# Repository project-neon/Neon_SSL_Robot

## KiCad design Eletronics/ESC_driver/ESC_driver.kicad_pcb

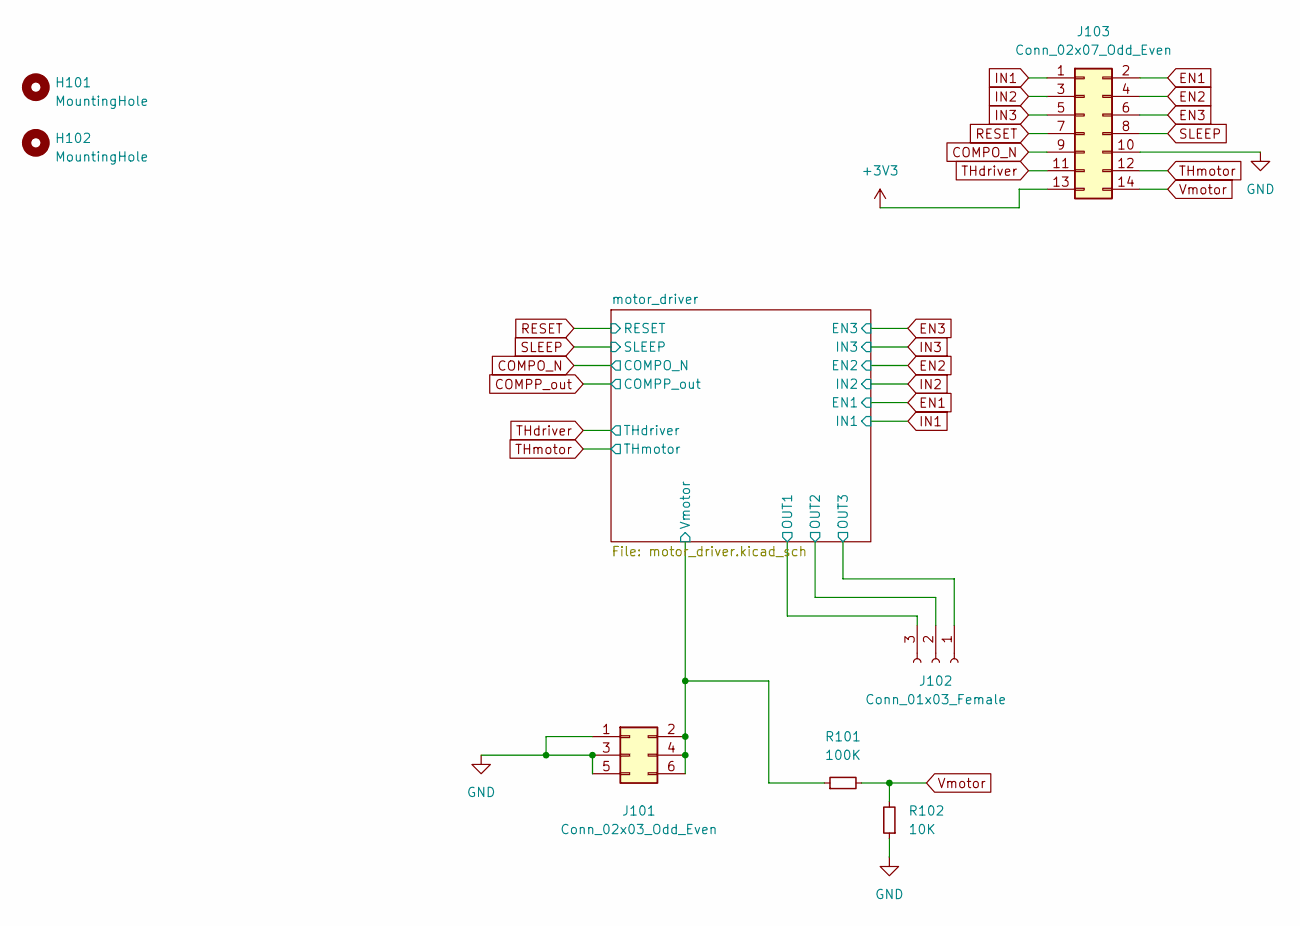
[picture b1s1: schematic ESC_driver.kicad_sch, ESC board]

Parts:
H101, H102: MountingHole; MountingHole_2.5mm
J101: Conn_02x03_Odd_Even; PinHeader_2x03_P2.54mm_Vertical; LCSC C65114
J102: Conn_01x03_Female; PinHeader_1x03_P2.54mm_Vertical; LCSC C6332196
J103: Conn_02x07_Odd_Even; PinHeader_2x07_P2.54mm_Vertical; LCSC C71397
R101: 100K; R_0603_1608Metric_Pad0.98x0.95mm_HandSolder; LCSC C14675
R102: 10K; R_0603_1608Metric_Pad0.98x0.95mm_HandSolder; LCSC C2930027

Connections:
+3V3: J103.13; also elsewhere on the board
/motor_driver/OUT1: J102.3; also elsewhere on the board
/motor_driver/OUT2: J102.2; also elsewhere on the board
/motor_driver/OUT3: J102.1; also elsewhere on the board
/motor_driver/VM_0.1_100uf: J101.2, J101.4, J101.6, R101.1; also elsewhere on the board
COMPO_N: J103.9; also elsewhere on the board
EN1: J103.2; also elsewhere on the board
EN2: J103.4; also elsewhere on the board
EN3: J103.6; also elsewhere on the board
GND: J101.1, J101.3, J101.5, J103.10, R102.1; also elsewhere on the board
IN1: J103.1; also elsewhere on the board
IN2: J103.3; also elsewhere on the board
IN3: J103.5; also elsewhere on the board
RESET: J103.7; also elsewhere on the board
SLEEP: J103.8; also elsewhere on the board
THdriver: J103.11; also elsewhere on the board
THmotor: J103.12; also elsewhere on the board
Vmotor: J103.14, R101.2, R102.2

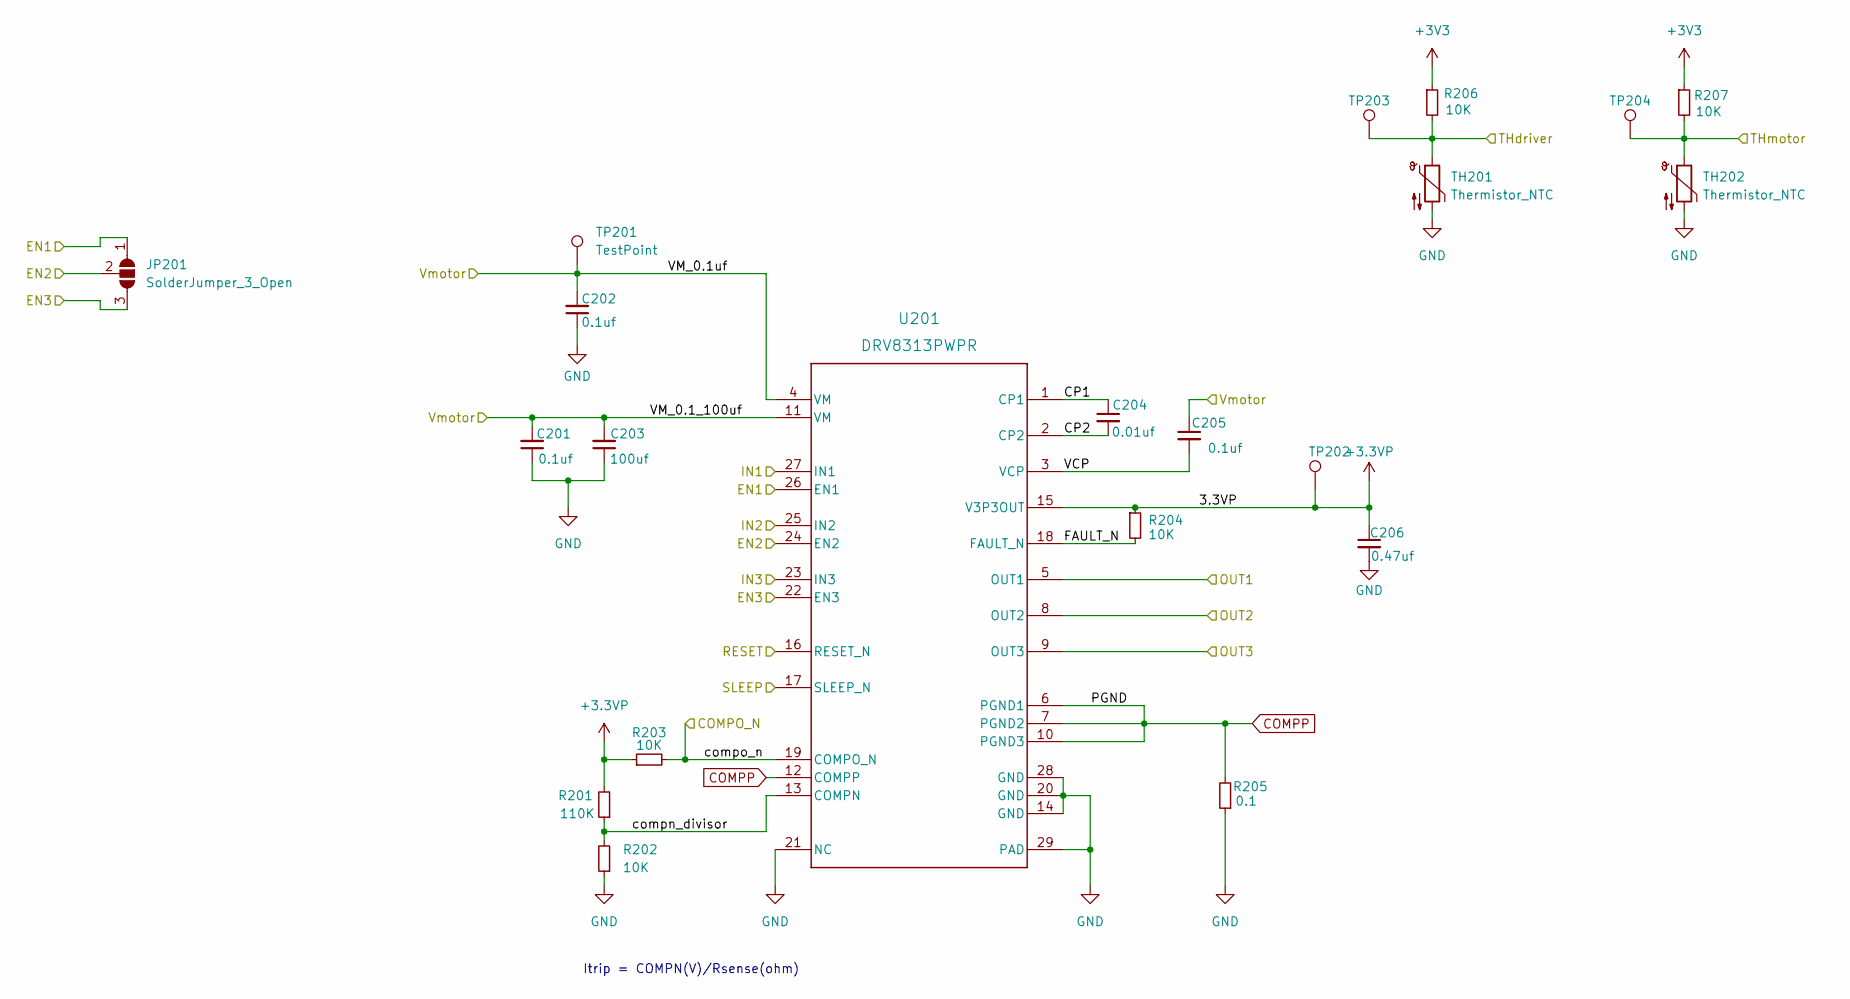
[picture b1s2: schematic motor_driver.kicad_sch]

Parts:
C201, C202, C205: 0.1uf; R_0603_1608Metric_Pad0.98x0.95mm_HandSolder; LCSC C14663
C203: 100uf; C_Elec_6.3x7.7; LCSC C72477
C204: 0.01uf; R_0603_1608Metric_Pad0.98x0.95mm_HandSolder; LCSC C1589
C206: 0.47uf; R_0603_1608Metric_Pad0.98x0.95mm_HandSolder; LCSC C105526
JP201: SolderJumper_3_Open; SolderJumper-3_P1.3mm_Open_RoundedPad1.0x1.5mm
R201: 110K; R_0603_1608Metric_Pad0.98x0.95mm_HandSolder; LCSC C25805
R202, R203, R204, R206, R207: 10K; R_0603_1608Metric_Pad0.98x0.95mm_HandSolder; LCSC C2930027
R205: 0.1; R_2512_6332Metric; LCSC C25466
TH201: Thermistor_NTC; R_0603_1608Metric_Pad0.98x0.95mm_HandSolder; LCSC C406719
TH202: Thermistor_NTC; PinHeader_1x02_P2.54mm_Vertical; LCSC C492401
TP201, TP202, TP203, TP204: TestPoint; TestPoint_Pad_D1.0mm
U201: DRV8313PWPR; PWP0028F_N; LCSC C92482

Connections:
+3.3VP: C206.1, R201.2, R203.1, R204.1, TP202.1, U201.15 (V3P3OUT)
+3V3: R206.1, R207.1; also elsewhere on the board
/motor_driver/CP1: C204.1, U201.1 (CP1)
/motor_driver/CP2: C204.2, U201.2 (CP2)
/motor_driver/FAULT_N: R204.2, U201.18 (FAULT_N)
/motor_driver/OUT1: U201.5 (OUT1); also elsewhere on the board
/motor_driver/OUT2: U201.8 (OUT2); also elsewhere on the board
/motor_driver/OUT3: U201.9 (OUT3); also elsewhere on the board
/motor_driver/VCP: C205.2, U201.3 (VCP)
/motor_driver/VM_0.1_100uf: C201.2, C202.2, C203.2, C205.1, TP201.1, U201.4 (VM), U201.11 (VM); also elsewhere on the board
/motor_driver/compn_divisor: R201.1, R202.2, U201.13 (COMPN)
COMPO_N: R203.2, U201.19 (COMPO_N); also elsewhere on the board
COMPP: R205.2, U201.6 (PGND1), U201.7 (PGND2), U201.10 (PGND3), U201.12 (COMPP)
EN1: JP201.1 (A), U201.26 (EN1); also elsewhere on the board
EN2: JP201.2 (C), U201.24 (EN2); also elsewhere on the board
EN3: JP201.3 (B), U201.22 (EN3); also elsewhere on the board
GND: C201.1, C202.1, C203.1, C206.2, R202.1, R205.1, TH201.2, TH202.2, U201.14 (GND), U201.20 (GND), U201.21 (NC), U201.28 (GND), U201.29 (PAD); also elsewhere on the board
IN1: U201.27 (IN1); also elsewhere on the board
IN2: U201.25 (IN2); also elsewhere on the board
IN3: U201.23 (IN3); also elsewhere on the board
RESET: U201.16 (RESET_N); also elsewhere on the board
SLEEP: U201.17 (SLEEP_N); also elsewhere on the board
THdriver: R206.2, TH201.1, TP203.1; also elsewhere on the board
THmotor: R207.2, TH202.1, TP204.1; also elsewhere on the board

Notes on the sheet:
Itrip = COMPN(V)/Rsense(ohm)

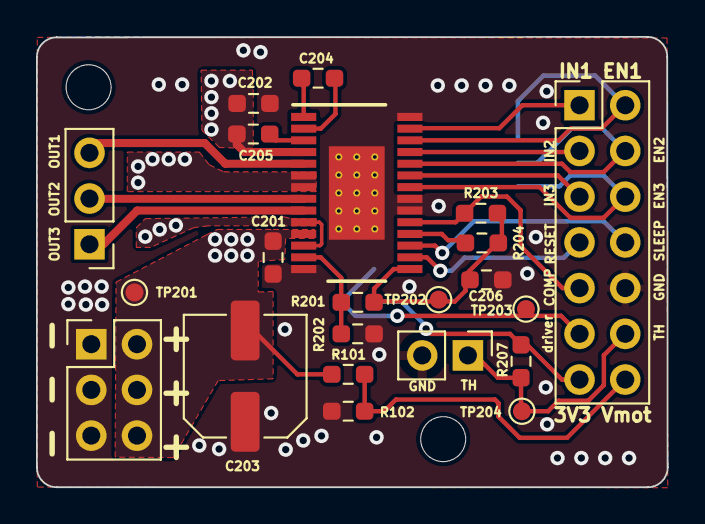
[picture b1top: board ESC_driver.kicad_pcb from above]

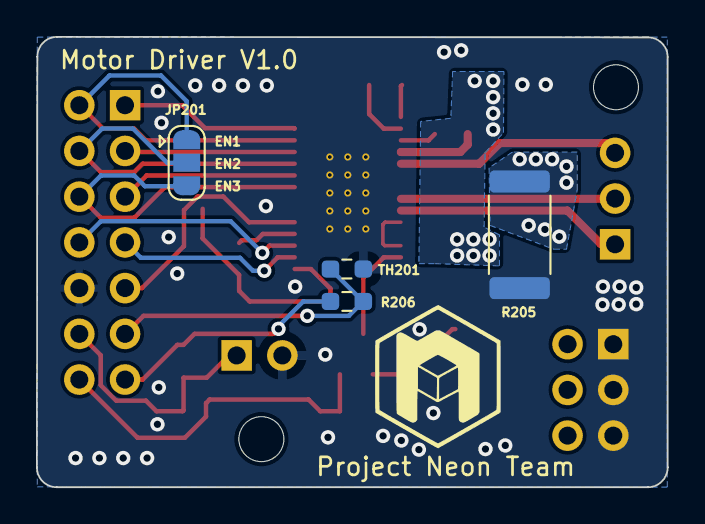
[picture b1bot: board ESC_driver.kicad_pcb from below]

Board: 2 copper layers, 35.0 x 25.0 mm, 28 parts (4 on the bottom side), 25 nets.

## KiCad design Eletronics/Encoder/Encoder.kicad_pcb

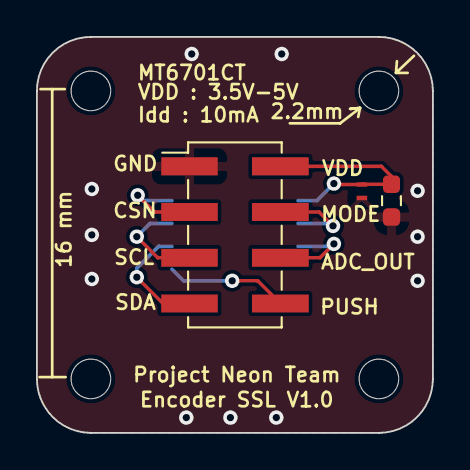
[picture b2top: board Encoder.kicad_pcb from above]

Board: 2 copper layers, 22.0 x 22.0 mm, 8 parts (1 on the bottom side), 8 nets.

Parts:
C201: 0.1UF; R_0603_1608Metric_Pad0.98x0.95mm_HandSolder
D201: VESD05A1B-HD1-GS08; VESD05A1B-HD1
H201, H202, H203, H204: MountingHole; MountingHole_2.2mm_M2
J201: Conn_02x04_Counter_Clockwise; PinHeader_2x04_P2.54mm_Vertical_SMD
U201: MT6701CT; SO-8_5.3x6.2mm_P1.27mm

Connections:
+3V3: C201.1, D201.1 (A1), J201.2, U201.1 (VDD)
ADC_out: J201.6, U201.3 (OUT)
A/SDA/DO: J201.7, U201.6 (A)
B/SCL/CLK: J201.5, U201.7 (B)
GND: C201.2, D201.2 (A2), J201.1, U201.4 (GND)
MODE: J201.4, U201.2 (MODE)
Z/CSN: J201.3, U201.8 (Z)
push: J201.8, U201.5 (PUSH)

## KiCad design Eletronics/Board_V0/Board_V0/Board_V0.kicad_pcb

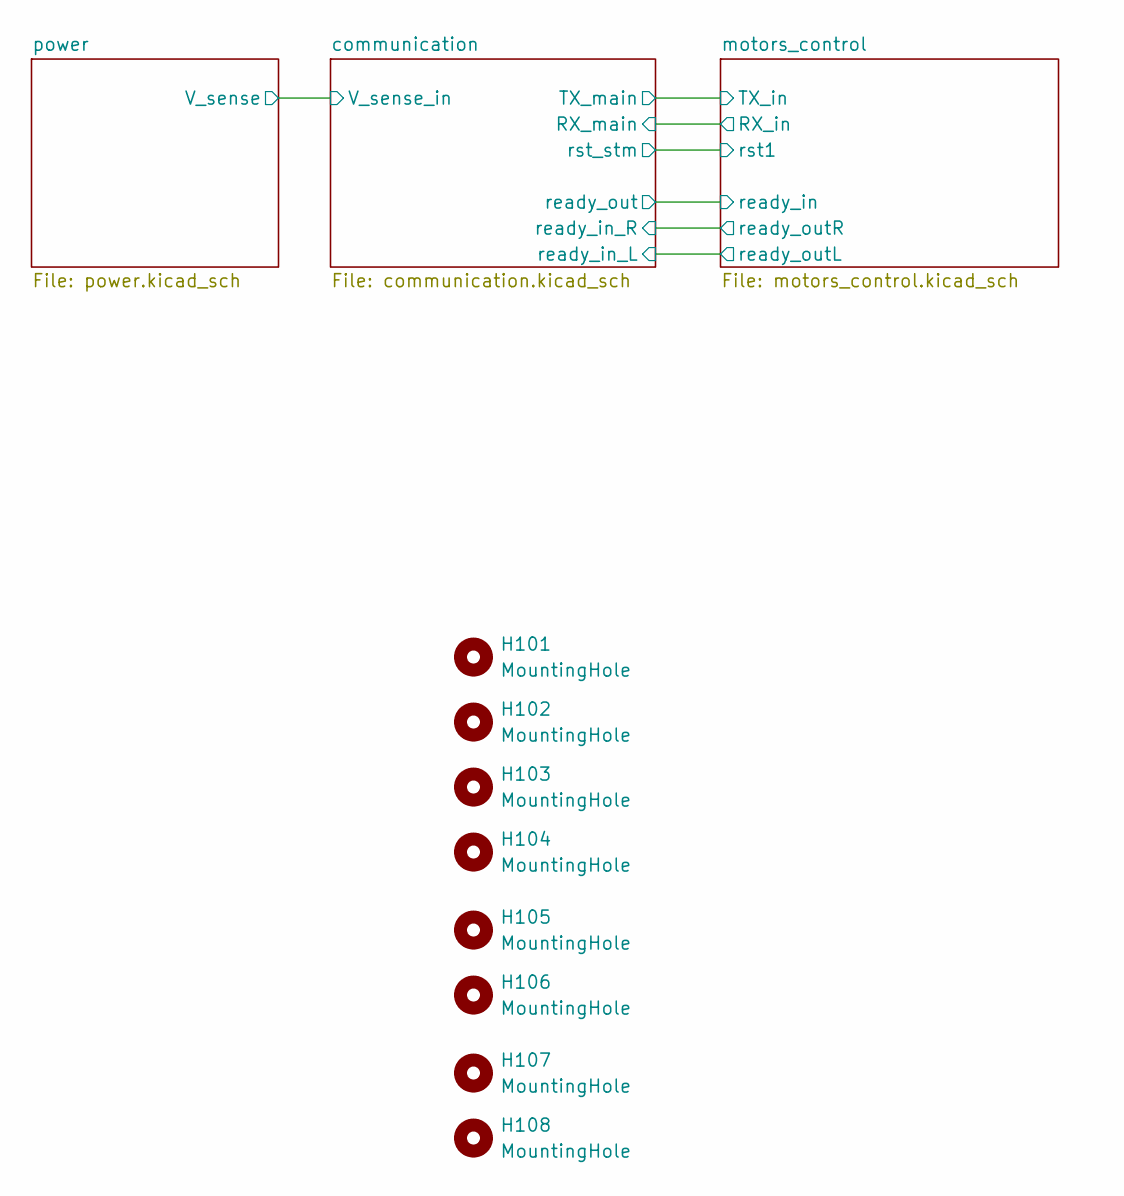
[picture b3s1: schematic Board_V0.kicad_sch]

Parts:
H101, H102, H103, H104, H105, H106, H107, H108: MountingHole; MountingHole_3.2mm_M3

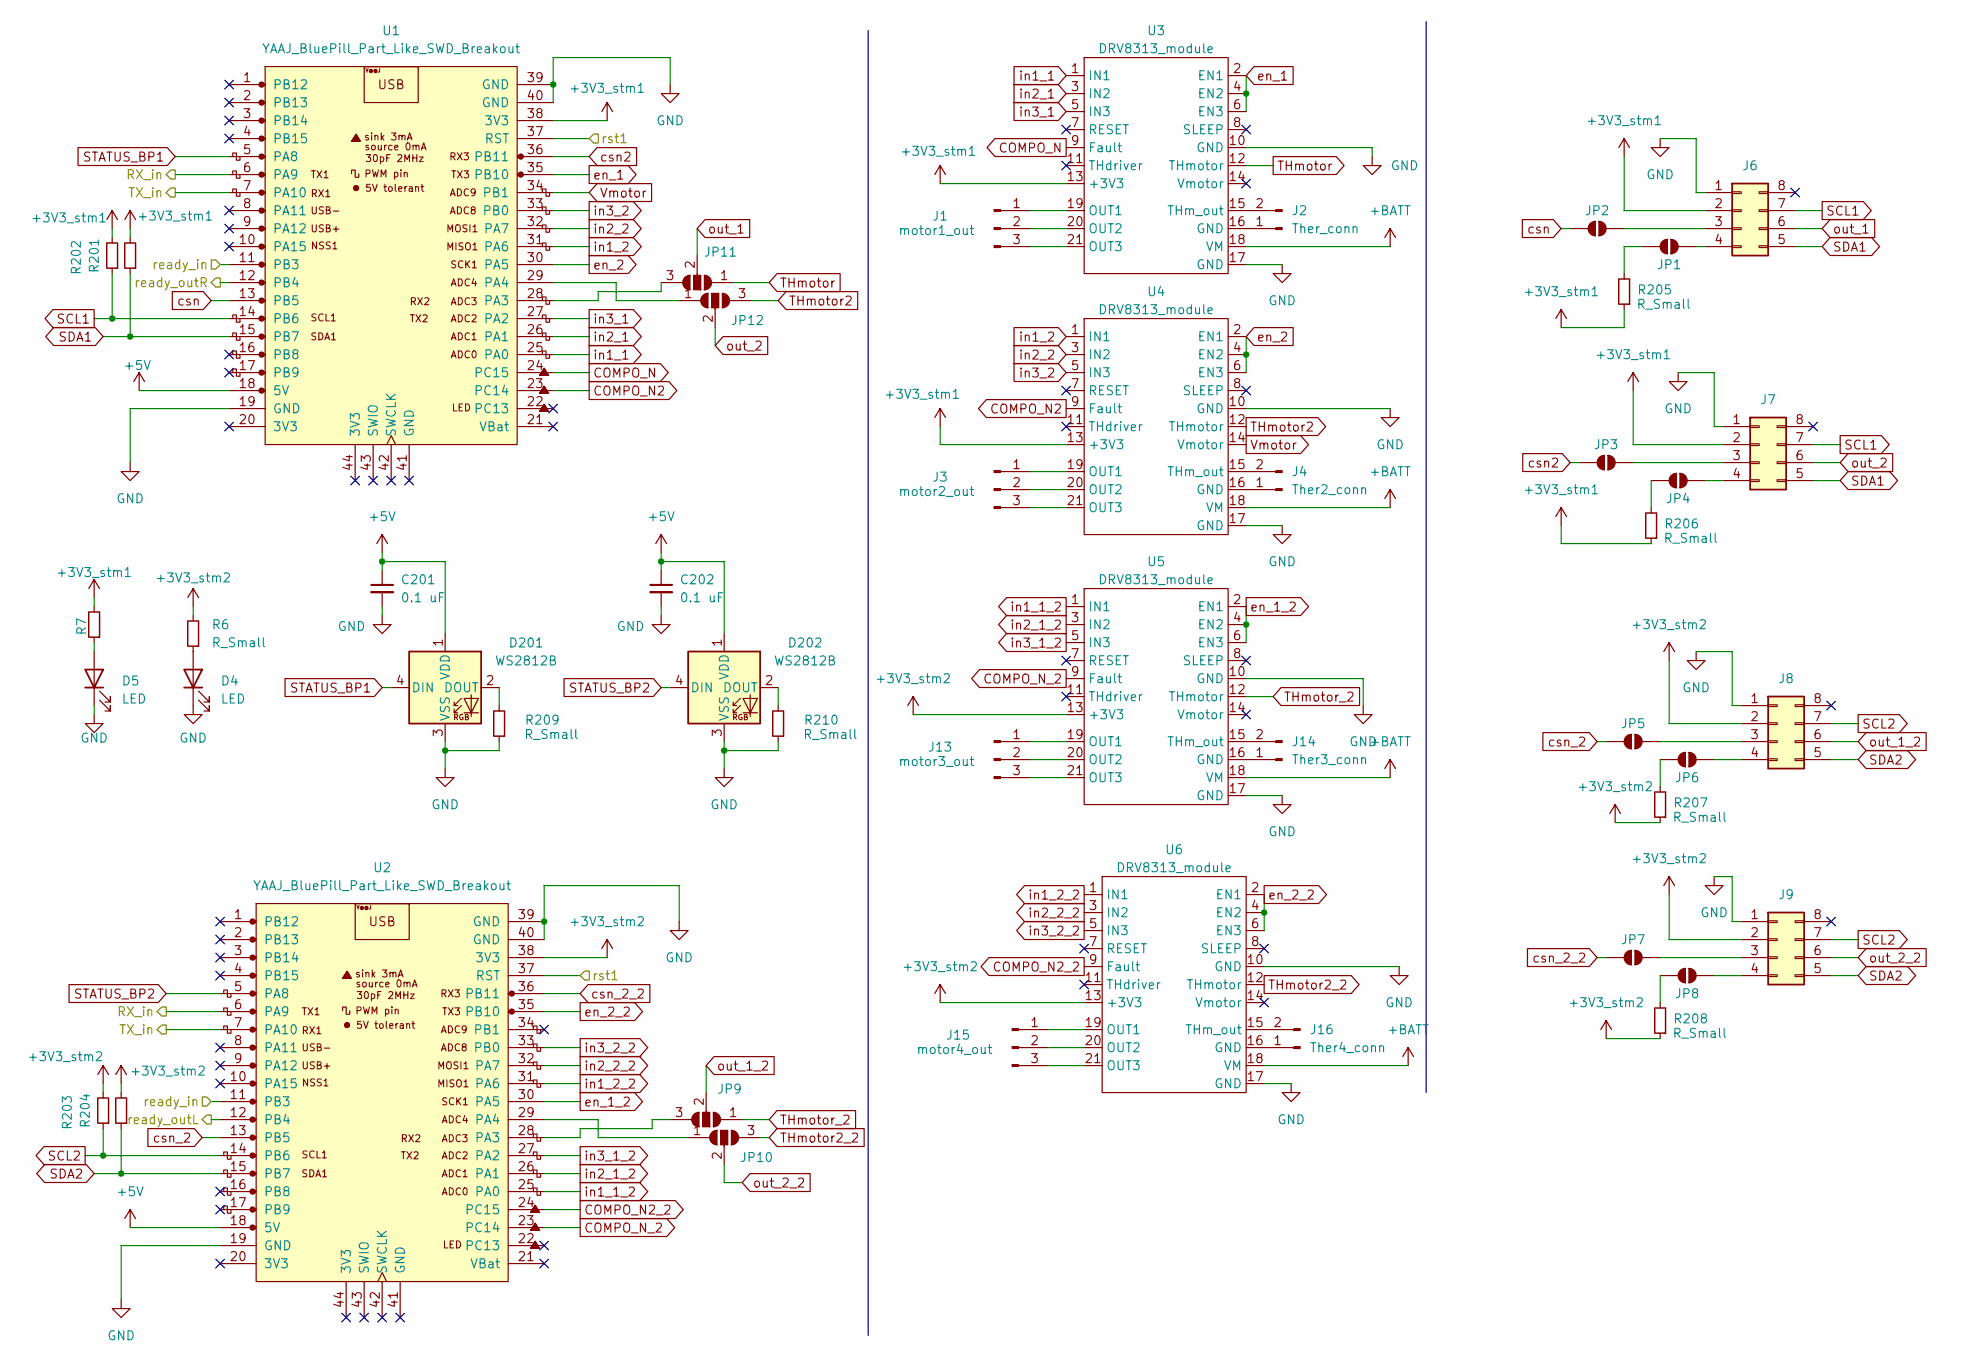
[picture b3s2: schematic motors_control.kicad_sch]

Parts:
C201, C202: 0.1 uF; C_0805_2012Metric
D4, D5: LED; LED_0805_2012Metric
D201, D202: WS2812B; LED_WS2812B_PLCC4_5.0x5.0mm_P3.2mm
J1: motor1_out; PinHeader_1x03_P2.54mm_Vertical
J2: Ther_conn; PinHeader_1x02_P2.54mm_Vertical
J3: motor2_out; PinHeader_1x03_P2.54mm_Vertical
J4: Ther2_conn; PinHeader_1x02_P2.54mm_Vertical
J6, J7, J8, J9: Conn_02x04_Counter_Clockwise; PinSocket_2x04_P2.54mm_Vertical
J13: motor3_out; PinHeader_1x03_P2.54mm_Vertical
J14: Ther3_conn; PinHeader_1x02_P2.54mm_Vertical
J15: motor4_out; PinHeader_1x03_P2.54mm_Vertical
J16: Ther4_conn; PinHeader_1x02_P2.54mm_Vertical
JP1, JP2, JP3, JP4, JP5, JP6, JP7, JP8: SolderJumper_2_Open; SolderJumper-2_P1.3mm_Open_RoundedPad1.0x1.5mm
JP9, JP10, JP11, JP12: SolderJumper_3_Open; SolderJumper-3_P1.3mm_Open_RoundedPad1.0x1.5mm
R6, R7, R201, R202, R203, R204, R205, R206, R207, R208, R209, R210: R_Small; R_0805_2012Metric_Pad1.20x1.40mm_HandSolder
U1, U2: YAAJ_BluePill_Part_Like_SWD_Breakout; YAAJ_BluePill_SWD_1
U3, U4, U5, U6: DRV8313_module; drv8313

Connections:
+3V3_stm1: J6.2, J7.2, R7.2, R201.2, R202.2, R205.1, R206.1, U1.38 (3V3), U3.13 (+3V3), U4.13 (+3V3)
+3V3_stm2: J8.2, J9.2, R6.2, R203.2, R204.2, R207.1, R208.1, U2.38 (3V3), U5.13 (+3V3), U6.13 (+3V3)
+5V: C201.1, C202.1, D201.1 (VDD), D202.1 (VDD), U1.18 (5V), U2.18 (5V); also elsewhere on the board
+BATT: U3.18 (VM), U4.18 (VM), U5.18 (VM), U6.18 (VM); also elsewhere on the board
-BATT: C201.2, C202.2, D4.1 (K), D5.1 (K), D201.3 (VSS), D202.3 (VSS), J6.1, J7.1, J8.1, J9.1, R209.1, R210.1, U1.19 (GND), U1.39 (GND), U1.40 (GND), U2.19 (GND), U2.39 (GND), U2.40 (GND), U3.10 (GND), U3.17 (GND), U4.10 (GND), U4.17 (GND), U5.10 (GND), U5.17 (GND), U6.10 (GND), U6.17 (GND); also elsewhere on the board
/communication/RX_main: U1.6 (PA9), U2.6 (PA9); also elsewhere on the board
/communication/TX_main: U1.7 (PA10), U2.7 (PA10); also elsewhere on the board
/communication/ready_in_L: U2.12 (PB4); also elsewhere on the board
/communication/ready_in_R: U1.12 (PB4); also elsewhere on the board
/communication/ready_out: U1.11 (PB3), U2.11 (PB3); also elsewhere on the board
/communication/rst_stm: U1.37 (RST), U2.37 (RST); also elsewhere on the board
COMPO_N: U1.24 (PC15), U3.9 (Fault)
COMPO_N2: U1.23 (PC14), U4.9 (Fault)
COMPO_N2_2: U2.24 (PC15), U6.9 (Fault)
COMPO_N_2: U2.23 (PC14), U5.9 (Fault)
unnamed: D4.2 (A), R6.1
unnamed: D5.2 (A), R7.1
unnamed: D201.2 (DOUT), R209.2
unnamed: D202.2 (DOUT), R210.2
unnamed: J1.1, U3.19 (OUT1)
unnamed: J1.2, U3.20 (OUT2)
unnamed: J1.3, U3.21 (OUT3)
unnamed: J2.1, U3.16 (GND)
unnamed: J2.2, U3.15 (THm_out)
unnamed: J3.1, U4.19 (OUT1)
unnamed: J3.2, U4.20 (OUT2)
unnamed: J3.3, U4.21 (OUT3)
unnamed: J4.1, U4.16 (GND)
unnamed: J4.2, U4.15 (THm_out)
unnamed: J6.3, JP2.1 (A)
unnamed: J6.4, JP1.1 (A)
unnamed: J7.3, JP3.1 (A)
unnamed: J7.4, JP4.1 (A)
unnamed: J8.3, JP5.1 (A)
unnamed: J8.4, JP6.1 (A)
unnamed: J9.3, JP7.1 (A)
unnamed: J9.4, JP8.1 (A)
unnamed: J13.1, U5.19 (OUT1)
unnamed: J13.2, U5.20 (OUT2)
unnamed: J13.3, U5.21 (OUT3)
unnamed: J14.1, U5.16 (GND)
unnamed: J14.2, U5.15 (THm_out)
unnamed: J15.1, U6.19 (OUT1)
unnamed: J15.2, U6.20 (OUT2)
unnamed: J15.3, U6.21 (OUT3)
unnamed: J16.1, U6.16 (GND)
unnamed: J16.2, U6.15 (THm_out)
unnamed: JP1.2 (B), R205.2
unnamed: JP4.2 (B), R206.2
unnamed: JP6.2 (B), R207.2
unnamed: JP8.2 (B), R208.2
unnamed: JP9.3 (B), U2.28 (PA3)
unnamed: JP10.1 (A), U2.29 (PA4)
unnamed: JP11.3 (B), U1.28 (PA3)
unnamed: JP12.1 (A), U1.29 (PA4)
SCL1: J6.7, J7.7, R202.1, U1.14 (PB6)
SCL2: J8.7, J9.7, R203.1, U2.14 (PB6)
SDA1: J6.5, J7.5, R201.1, U1.15 (PB7)
SDA2: J8.5, J9.5, R204.1, U2.15 (PB7)
STATUS_BP1: D201.4 (DIN), U1.5 (PA8)
STATUS_BP2: D202.4 (DIN), U2.5 (PA8)
THmotor: JP11.1 (A), U3.12 (THmotor)
THmotor2: JP12.3 (B), U4.12 (THmotor)
THmotor2_2: JP10.3 (B), U6.12 (THmotor)
THmotor_2: JP9.1 (A), U5.12 (THmotor)
Vmotor: U1.34 (PB1), U4.14 (Vmotor)
csn: JP2.2 (B), U1.13 (PB5)
csn2: JP3.2 (B), U1.36 (PB11)
csn_2: JP5.2 (B), U2.13 (PB5)
csn_2_2: JP7.2 (B), U2.36 (PB11)
en_1: U1.35 (PB10), U3.2 (EN1), U3.4 (EN2), U3.6 (EN3)
en_1_2: U2.30 (PA5), U5.2 (EN1), U5.4 (EN2), U5.6 (EN3)
en_2: U1.30 (PA5), U4.2 (EN1), U4.4 (EN2), U4.6 (EN3)
en_2_2: U2.35 (PB10), U6.2 (EN1), U6.4 (EN2), U6.6 (EN3)
in1_1: U1.25 (PA0), U3.1 (IN1)
in1_1_2: U2.25 (PA0), U5.1 (IN1)
in1_2: U1.31 (PA6), U4.1 (IN1)
in1_2_2: U2.31 (PA6), U6.1 (IN1)
in2_1: U1.26 (PA1), U3.3 (IN2)
in2_1_2: U2.26 (PA1), U5.3 (IN2)
in2_2: U1.32 (PA7), U4.3 (IN2)
in2_2_2: U2.32 (PA7), U6.3 (IN2)
in3_1: U1.27 (PA2), U3.5 (IN3)
in3_1_2: U2.27 (PA2), U5.5 (IN3)
in3_2: U1.33 (PB0), U4.5 (IN3)
in3_2_2: U2.33 (PB0), U6.5 (IN3)
out_1: J6.6, JP11.2 (C)
out_1_2: J8.6, JP9.2 (C)
out_2: J7.6, JP12.2 (C)
out_2_2: J9.6, JP10.2 (C)

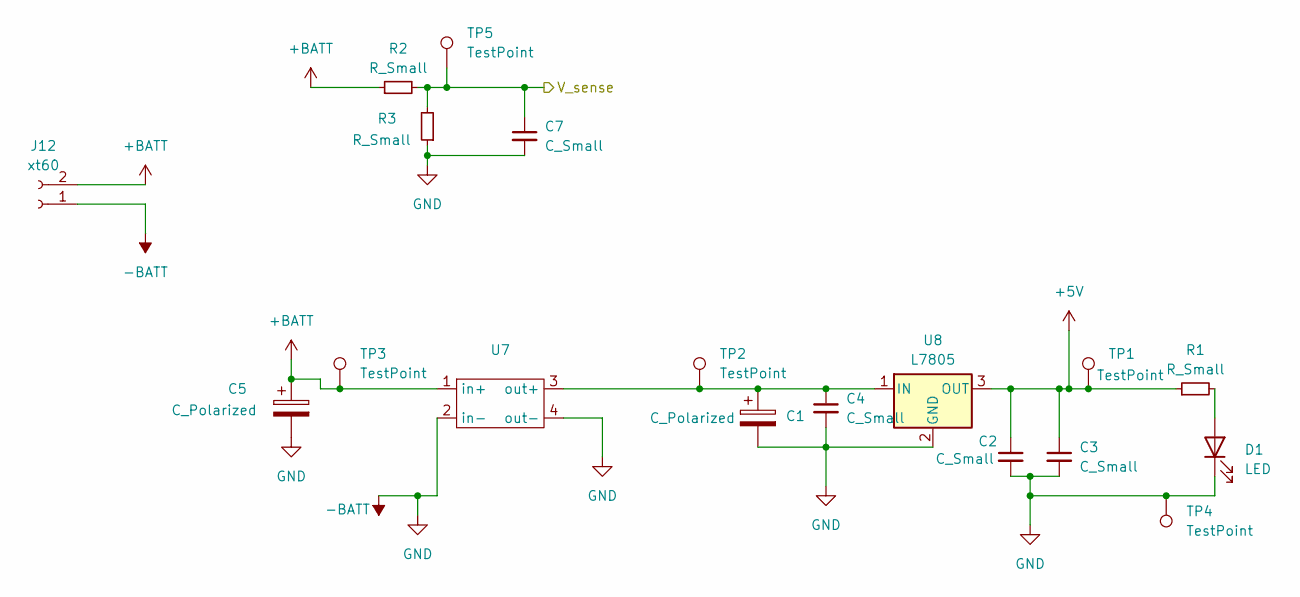
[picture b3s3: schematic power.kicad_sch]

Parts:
C1: C_Polarized; CP_Radial_D12.5mm_P5.00mm
C2, C3, C4, C7: C_Small; C_0805_2012Metric_Pad1.18x1.45mm_HandSolder
C5: C_Polarized; CP_Radial_D22.0mm_P10.00mm_SnapIn
D1: LED; LED_0805_2012Metric
J12: xt60; AMASS_XT60-M_1x02_P7.20mm_Vertical
R1, R2, R3: R_Small; R_0805_2012Metric_Pad1.20x1.40mm_HandSolder
TP1, TP2, TP3, TP4, TP5: TestPoint; TestPoint_Pad_D1.5mm
U7: module_LM2596
U8: L7805; TO-220-3_Horizontal_TabDown

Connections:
+5V: C2.1, C3.1, R1.1, TP1.1, U8.3 (OUT); also elsewhere on the board
+BATT: C5.1, J12.2, R2.1, TP3.1, U7.1 (in+); also elsewhere on the board
-BATT: C1.2, C2.2, C3.2, C4.2, C5.2, C7.2, D1.1 (K), J12.1, R3.1, TP4.1, U7.2 (in-), U7.4 (out-), U8.2 (GND); also elsewhere on the board
/communication/V_sense_in: C7.1, R2.2, R3.2, TP5.1; also elsewhere on the board
unnamed: D1.2 (A), R1.2
unnamed: C1.1, C4.1, TP2.1, U7.3 (out+), U8.1 (IN)

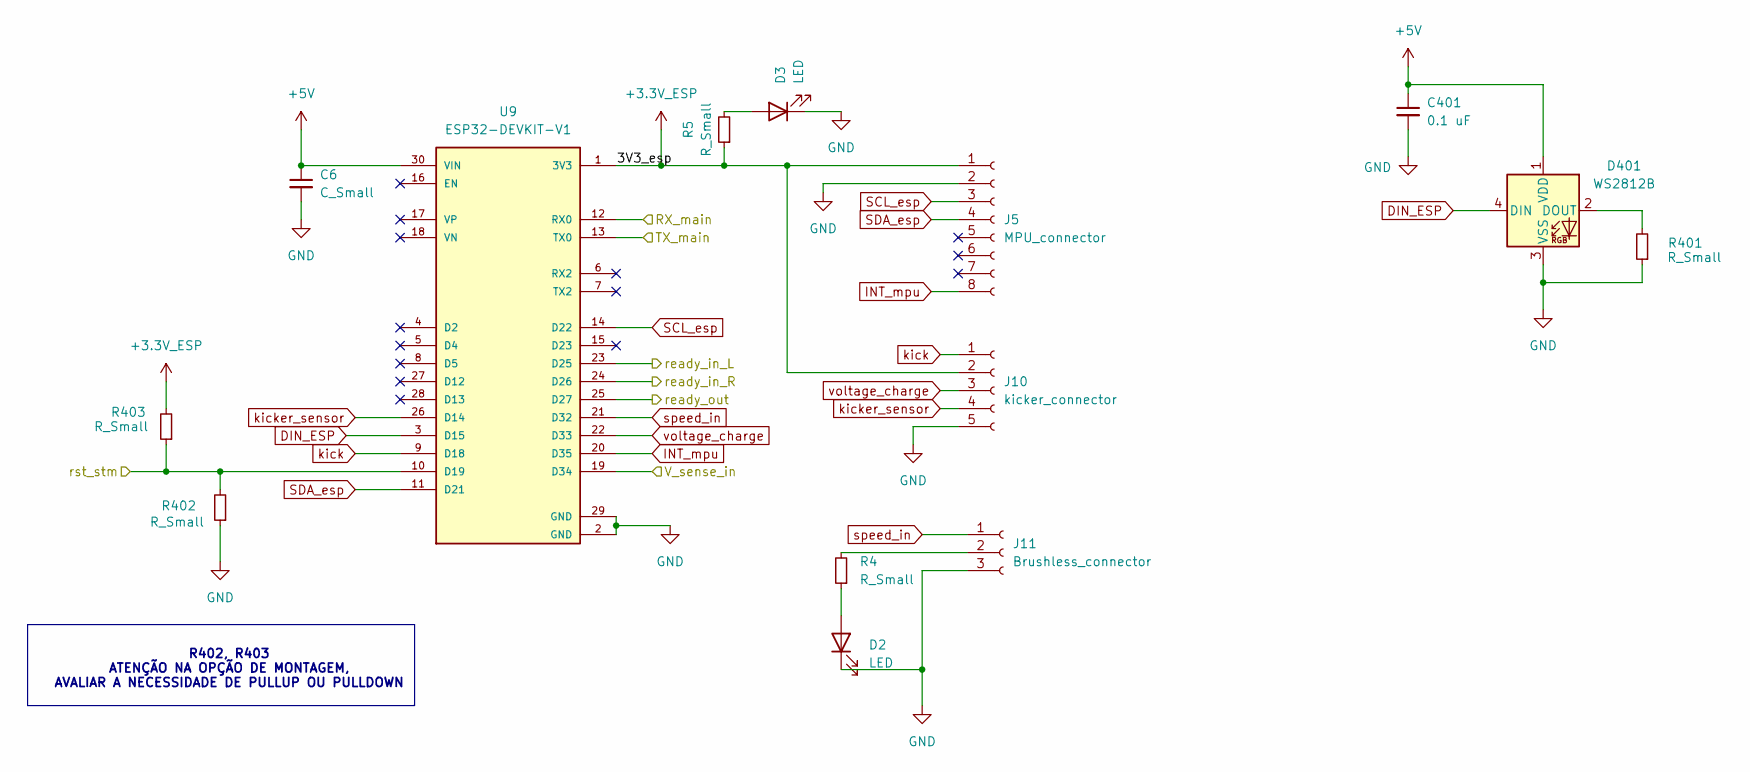
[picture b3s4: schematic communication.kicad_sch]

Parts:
C6: C_Small; C_0805_2012Metric_Pad1.18x1.45mm_HandSolder
C401: 0.1 uF; C_0805_2012Metric
D2, D3: LED; LED_0805_2012Metric
D401: WS2812B; LED_WS2812B_PLCC4_5.0x5.0mm_P3.2mm
J5: MPU_connector; modulo_mpu6050
J10: kicker_connector; PinSocket_1x05_P2.54mm_Vertical
J11: Brushless_connector; PinSocket_1x03_P2.54mm_Vertical
R4, R5, R401, R402, R403: R_Small; R_0805_2012Metric_Pad1.20x1.40mm_HandSolder
U9: ESP32-DEVKIT-V1; esp32_dev_kit; PARTREV N/A

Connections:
+3.3V_ESP: J5.1, J10.2, R5.1, R403.2, U9.1 (3V3)
+5V: C6.1, C401.1, D401.1 (VDD), U9.30 (VIN); also elsewhere on the board
-BATT: C6.2, C401.2, D2.1 (K), D3.1 (K), D401.3 (VSS), J5.2, J10.5, J11.3, R401.1, R402.1, U9.2 (GND), U9.29 (GND); also elsewhere on the board
/communication/RX_main: U9.12 (RX0); also elsewhere on the board
/communication/TX_main: U9.13 (TX0); also elsewhere on the board
/communication/V_sense_in: U9.19 (D34); also elsewhere on the board
/communication/ready_in_L: U9.23 (D25); also elsewhere on the board
/communication/ready_in_R: U9.24 (D26); also elsewhere on the board
/communication/ready_out: U9.25 (D27); also elsewhere on the board
/communication/rst_stm: R402.2, R403.1, U9.10 (D19); also elsewhere on the board
DIN_ESP: D401.4 (DIN), U9.3 (D15)
INT_mpu: J5.8, U9.20 (D35)
unnamed: D2.2 (A), R4.1
unnamed: D3.2 (A), R5.2
unnamed: D401.2 (DOUT), R401.2
unnamed: J11.2, R4.2
SCL_esp: J5.3, U9.14 (D22)
SDA_esp: J5.4, U9.11 (D21)
kick: J10.1, U9.9 (D18)
kicker_sensor: J10.4, U9.26 (D14)
speed_in: J11.1, U9.21 (D32)
voltage_charge: J10.3, U9.22 (D33)

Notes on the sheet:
R402, R403 ATENÇÃO NA OPÇÃO DE MONTAGEM, AVALIAR A NECESSIDADE DE PULLUP OU PULLDOWN

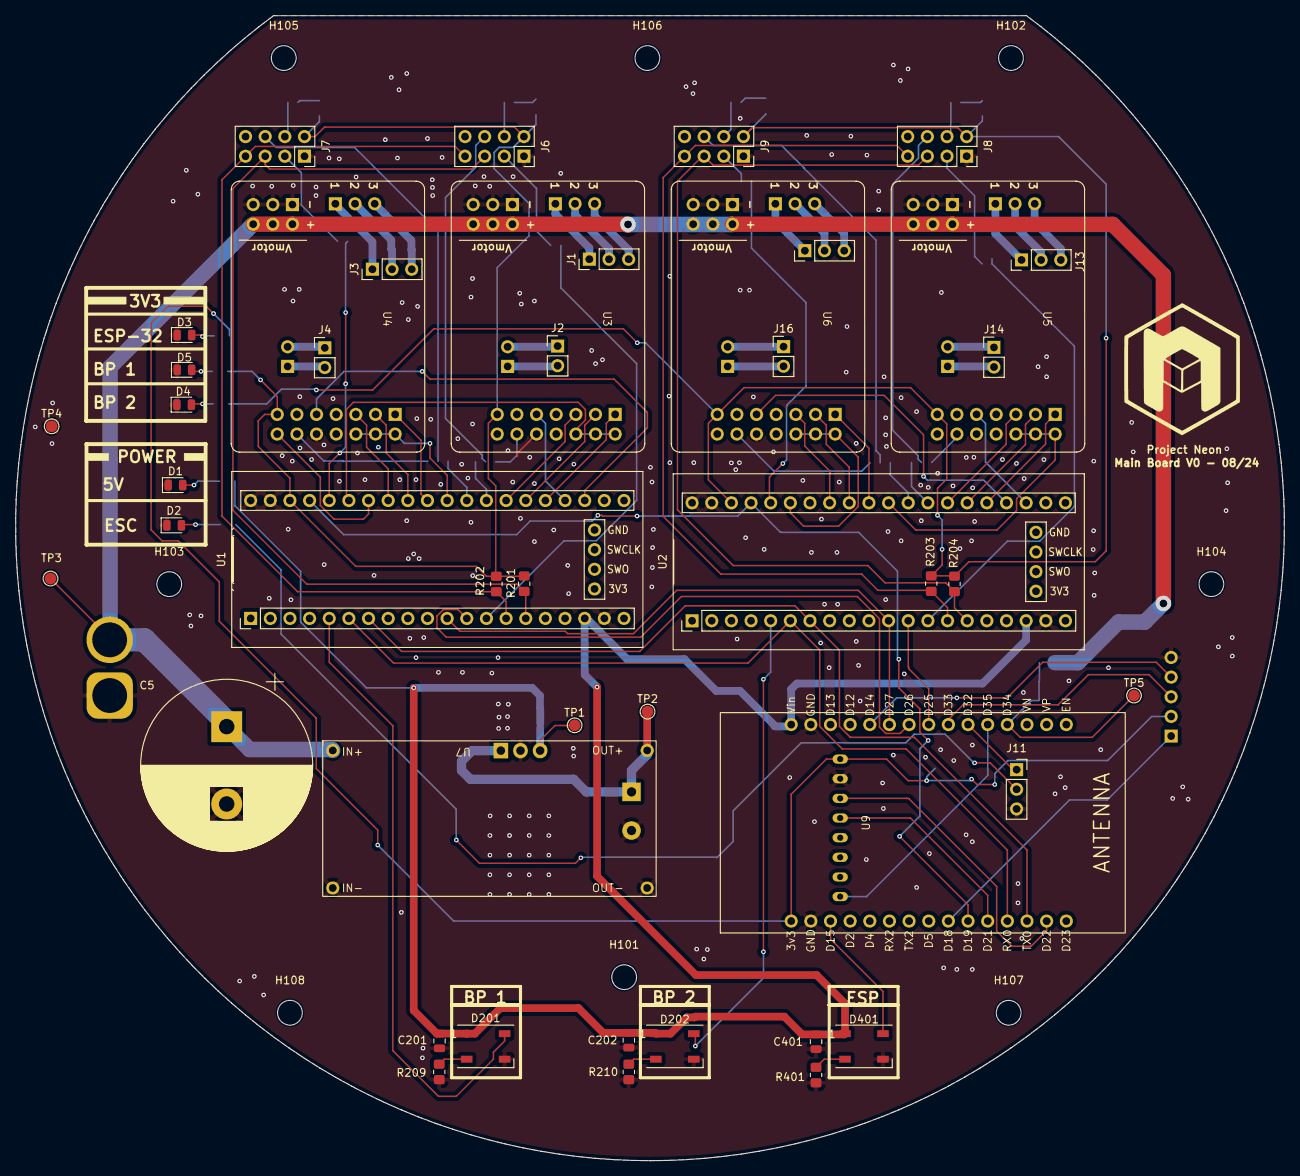
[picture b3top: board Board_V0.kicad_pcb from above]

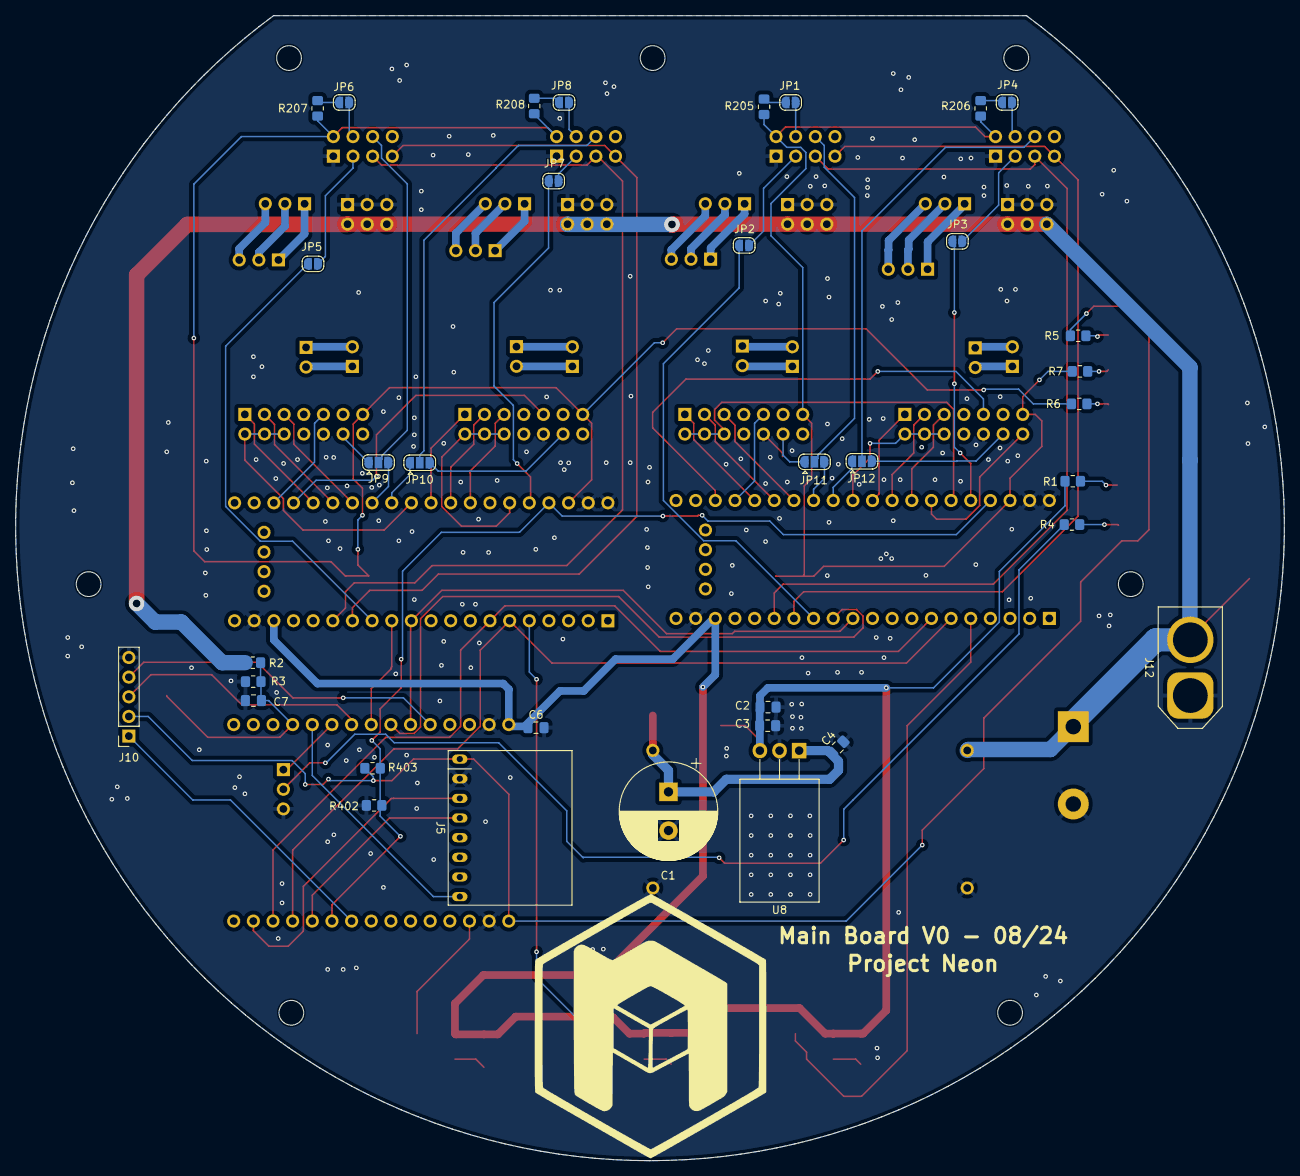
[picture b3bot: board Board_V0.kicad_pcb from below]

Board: 2 copper layers, 164.0 x 148.0 mm, 88 parts (35 on the bottom side), 106 nets.

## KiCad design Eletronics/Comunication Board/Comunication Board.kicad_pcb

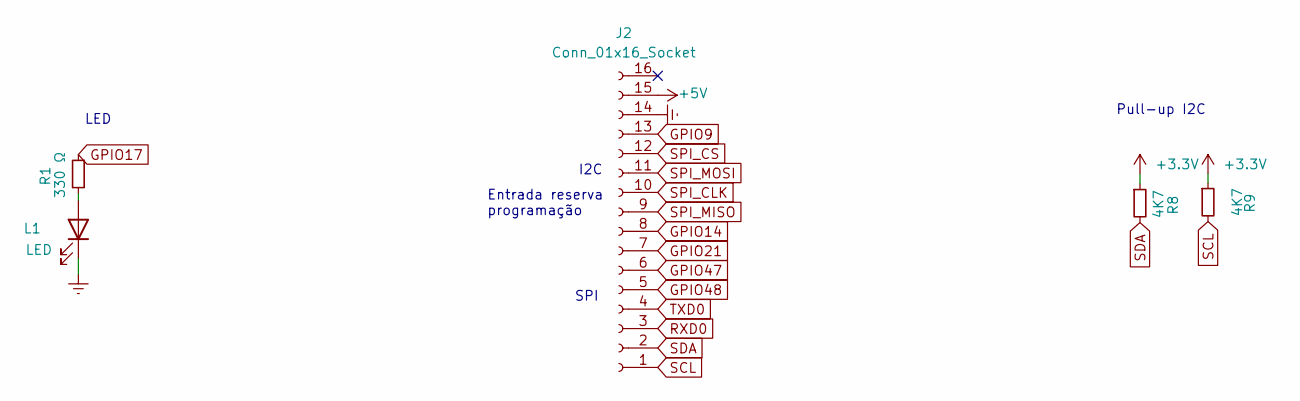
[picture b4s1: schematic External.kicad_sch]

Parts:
J2: Conn_01x16_Socket; IDC-Header_2x08_P2.54mm_Vertical
L1: LED; LED_0603_1608Metric
R1: 330 Ω; R_0603_1608Metric
R8, R9: 4K7; R_0603_1608Metric

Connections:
+3.3V: R8.1, R9.1; also elsewhere on the board
+5V: J2.15; also elsewhere on the board
GNDREF: J2.14, L1.1 (K); also elsewhere on the board
GPIO9: J2.13; also elsewhere on the board
GPIO14: J2.8; also elsewhere on the board
GPIO17: R1.1; also elsewhere on the board
GPIO21: J2.7; also elsewhere on the board
GPIO47: J2.6; also elsewhere on the board
GPIO48: J2.5; also elsewhere on the board
unnamed: L1.2 (A), R1.2
RXD0: J2.3; also elsewhere on the board
SCL: J2.1, R9.2; also elsewhere on the board
SDA: J2.2, R8.2; also elsewhere on the board
SPI_CLK: J2.10; also elsewhere on the board
SPI_CS: J2.12; also elsewhere on the board
SPI_MISO: J2.9; also elsewhere on the board
SPI_MOSI: J2.11; also elsewhere on the board
TXD0: J2.4; also elsewhere on the board

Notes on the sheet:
I2C
LED
Entrada reserva programação
SPI
Pull-up I2C

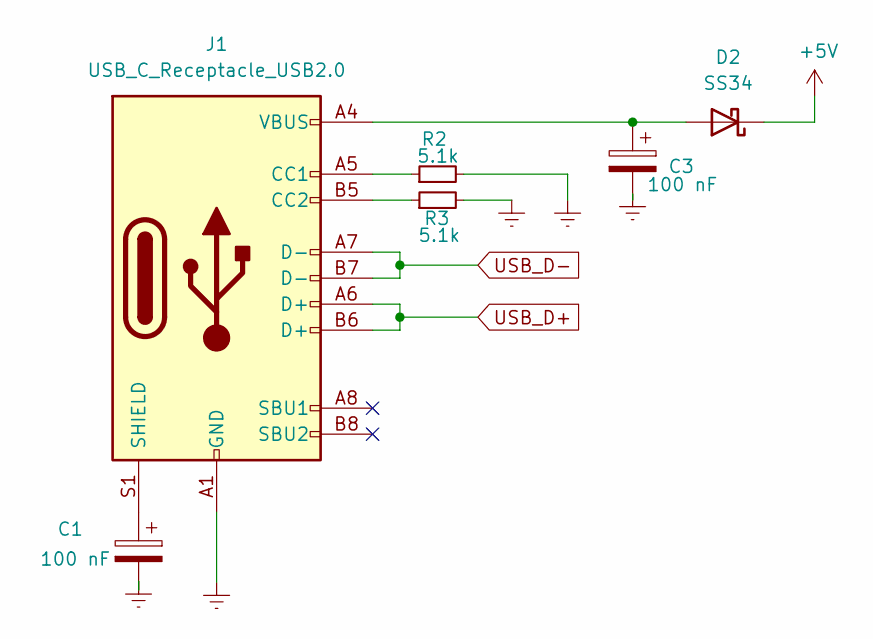
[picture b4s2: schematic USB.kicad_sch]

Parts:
C1, C3: 100 nF; C_0603_1608Metric
D2: SS34; D_SOD-123F
J1: USB_C_Receptacle_USB2.0; USB_C_Receptacle_KH-TYPE-C-16P
R2, R3: 5.1k; R_0603_1608Metric; LCSC C163928

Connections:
+5V: D2.1 (K); also elsewhere on the board
GNDREF: C1.2, C3.2, J1.A1 (GND), J1.A12 (GND), J1.B1 (GND), J1.B12 (GND), R2.2, R3.2; also elsewhere on the board
unnamed: C3.1, D2.2 (A), J1.A4 (VBUS), J1.A9 (VBUS), J1.B4 (VBUS), J1.B9 (VBUS)
unnamed: J1.A5 (CC1), R2.1
unnamed: J1.B5 (CC2), R3.1
unnamed: C1.1, J1.S1 (SHIELD)
USB_D+: J1.A6 (D+), J1.B6 (D+); also elsewhere on the board
USB_D-: J1.A7 (D-), J1.B7 (D-); also elsewhere on the board
